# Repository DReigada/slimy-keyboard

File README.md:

# Slimy

a cool description for a cool keyboard

## TODO

- PCB
    - [ ] holes for feet?

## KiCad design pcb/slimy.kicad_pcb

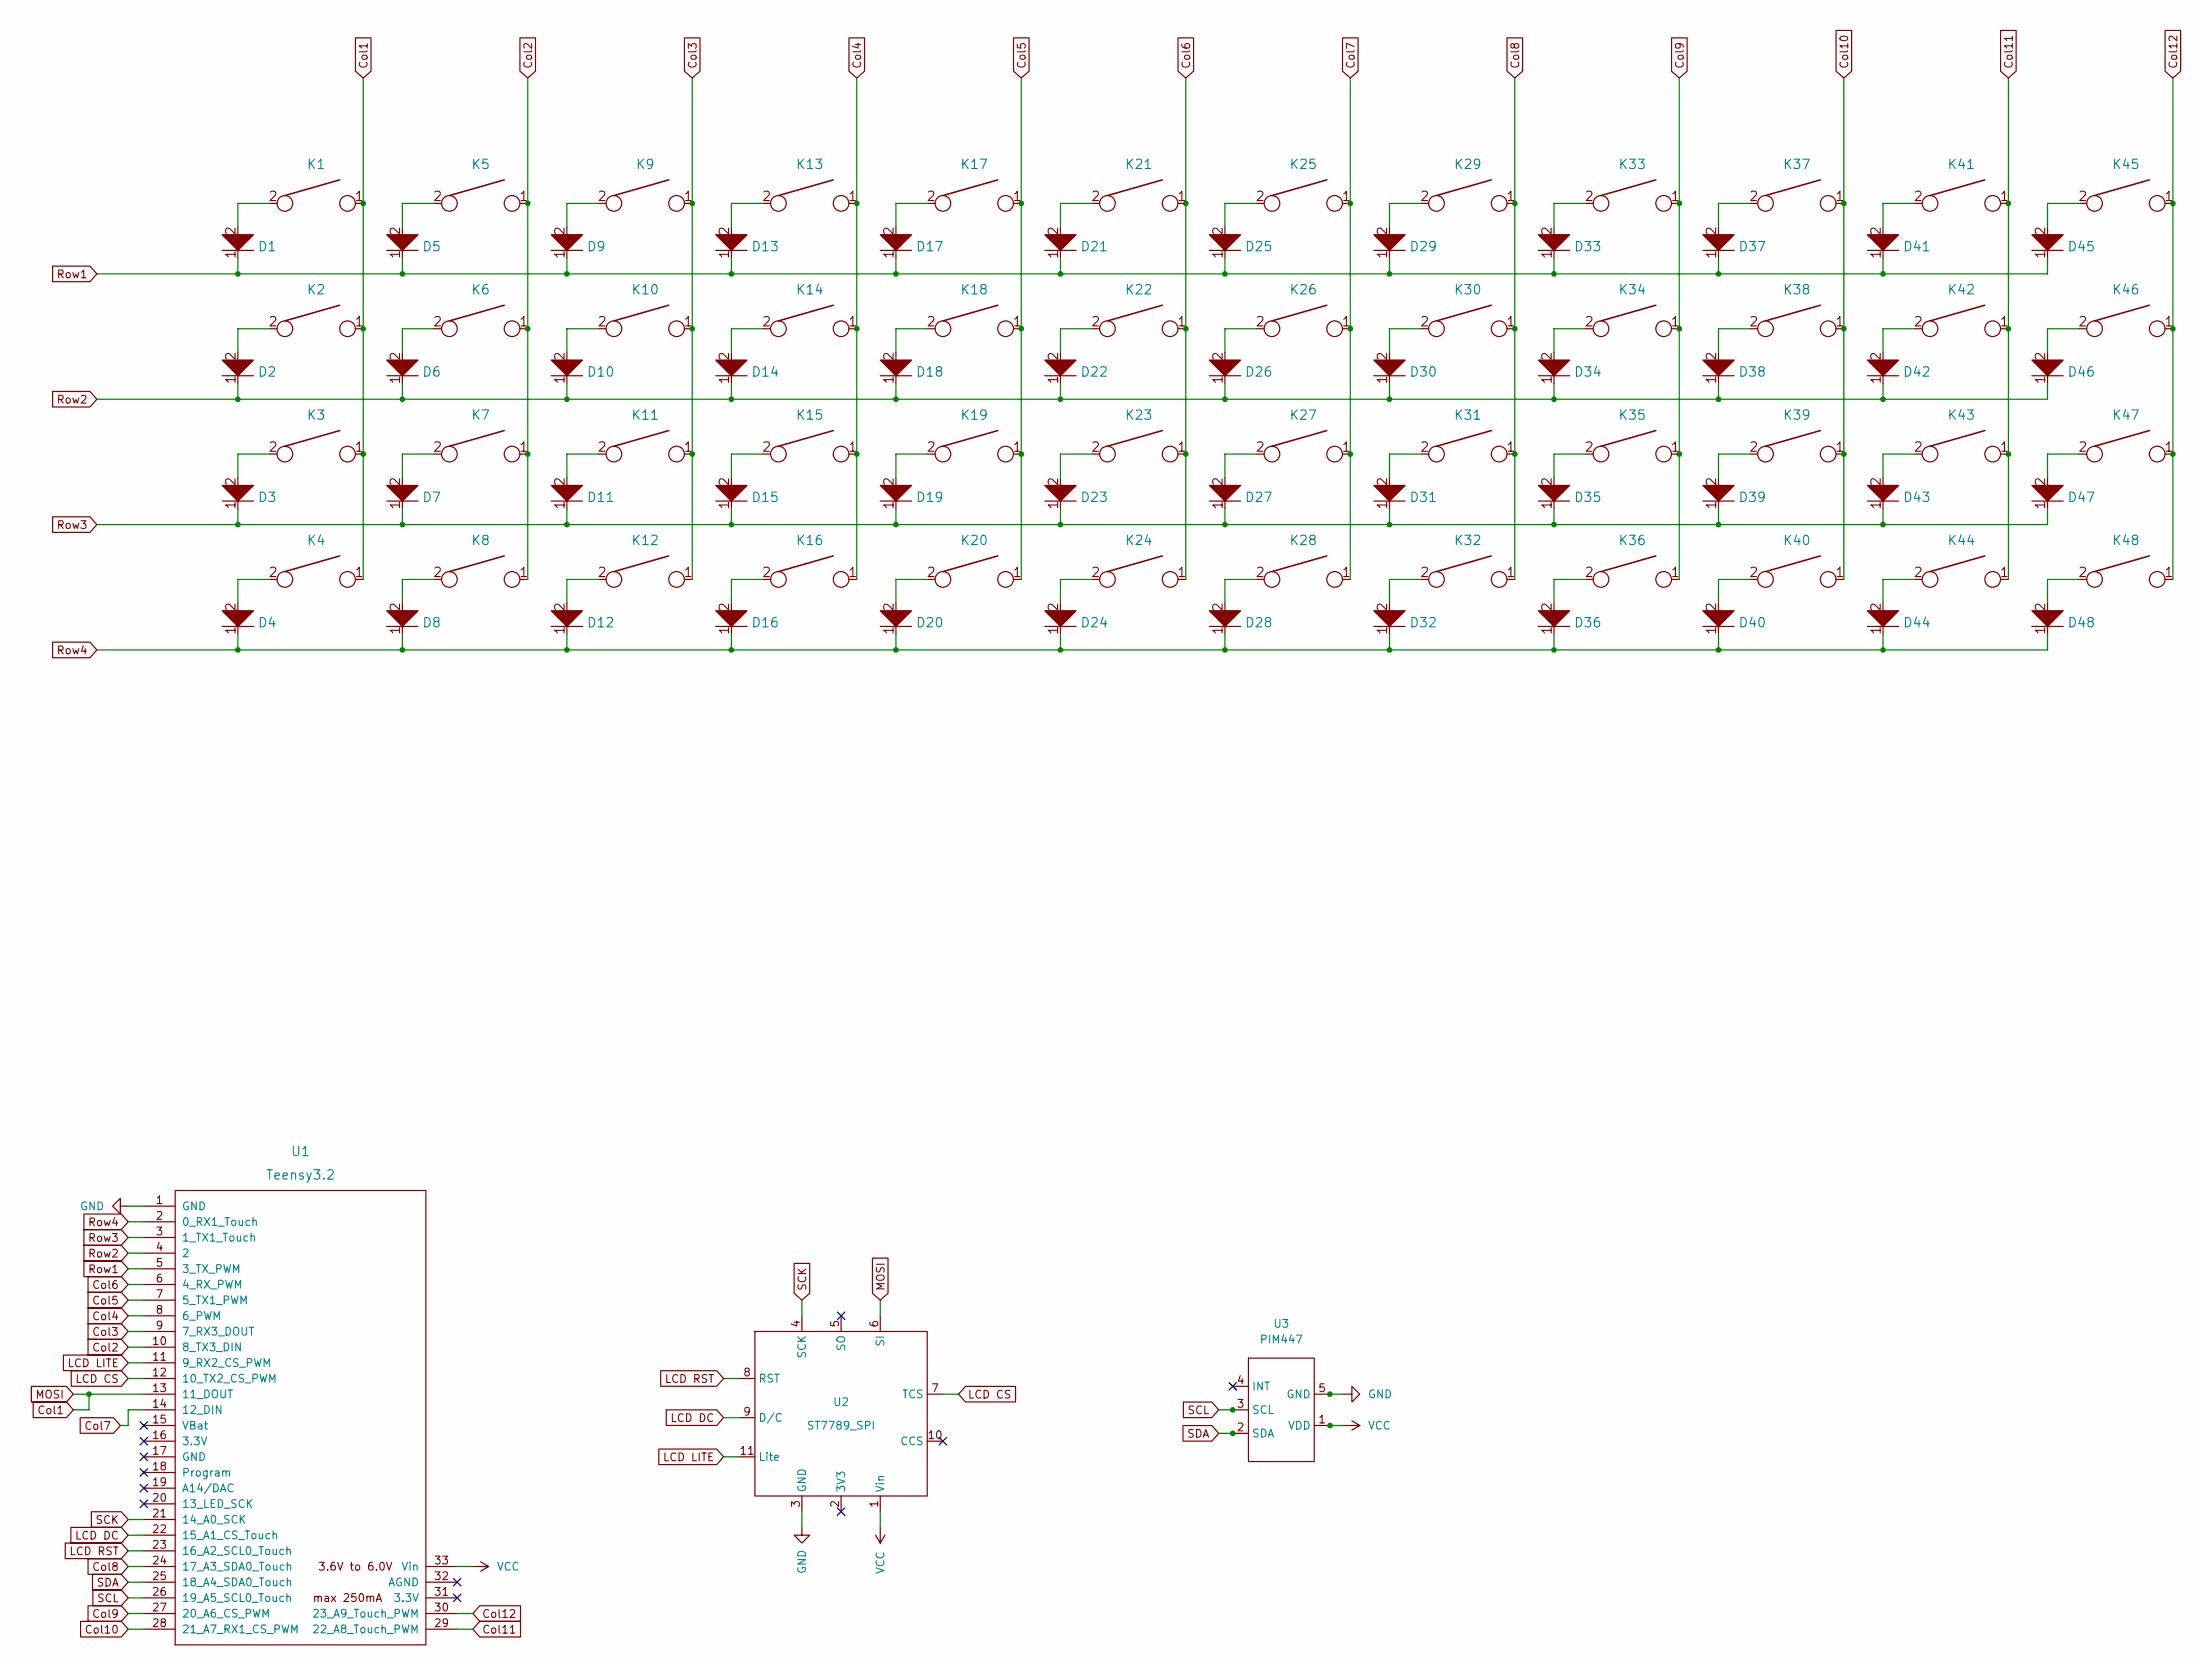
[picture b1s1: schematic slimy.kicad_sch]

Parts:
D1, D2, D3, D4, D5, D6, D7, D8, D9, D10, D11, D12, D13, D14, D15, D16, D17, D18, D19, D20, D21, D22, D23, D24, D25, D26, D27, D28, D29, D30, D31, D32, D33, D34, D35, D36, D37, D38, D39, D40, D41, D42, D43, D44, D45, D46, D47, D48: D
K1, K2, K3, K4, K5, K6, K7, K8, K9, K10, K11, K12, K13, K14, K15, K16, K17, K18, K19, K20, K21, K22, K23, K24, K25, K26, K27, K28, K29, K30, K31, K32, K33, K34, K35, K36, K37, K38, K39, K40, K41, K42, K43, K44, K45, K46, K47, K48: KEYSW; MX-1U-Hotswap-Antishear-flipped
U1: Teensy3.2; Teensy32
U2: ST7789_SPI; ST7789_1.3_240x240
U3: PIM447

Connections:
Col1: K1.1, K2.1, K3.1, K4.1, U1.13 (11_DOUT), U2.6 (SI)
Col2: K5.1, K6.1, K7.1, K8.1, U1.10 (8_TX3_DIN)
Col3: K9.1, K10.1, K11.1, K12.1, U1.9 (7_RX3_DOUT)
Col4: K13.1, K14.1, K15.1, K16.1, U1.8 (6_PWM)
Col5: K17.1, K18.1, K19.1, K20.1, U1.7 (5_TX1_PWM)
Col6: K21.1, K22.1, K23.1, K24.1, U1.6 (4_RX_PWM)
Col7: K25.1, K26.1, K27.1, K28.1, U1.14 (12_DIN)
Col8: K29.1, K30.1, K31.1, K32.1, U1.24 (17_A3_SDA0_Touch)
Col9: K33.1, K34.1, K35.1, K36.1, U1.27 (20_A6_CS_PWM)
Col10: K37.1, K38.1, K39.1, K40.1, U1.28 (21_A7_RX1_CS_PWM)
Col11: K41.1, K42.1, K43.1, K44.1, U1.29 (22_A8_Touch_PWM)
Col12: K45.1, K46.1, K47.1, K48.1, U1.30 (23_A9_Touch_PWM)
GND: U1.1 (GND), U2.3 (GND), U3.5 (GND)
LCD CS: U1.12 (10_TX2_CS_PWM), U2.7 (TCS)
LCD DC: U1.22 (15_A1_CS_Touch), U2.9 (D/C)
LCD LITE: U1.11 (9_RX2_CS_PWM), U2.11 (Lite)
LCD RST: U1.23 (16_A2_SCL0_Touch), U2.8 (RST)
unnamed: D1.2, K1.2
unnamed: D2.2, K2.2
unnamed: D3.2, K3.2
unnamed: D4.2, K4.2
unnamed: D5.2, K5.2
unnamed: D6.2, K6.2
unnamed: D7.2, K7.2
unnamed: D8.2, K8.2
unnamed: D9.2, K9.2
unnamed: D10.2, K10.2
unnamed: D11.2, K11.2
unnamed: D12.2, K12.2
unnamed: D13.2, K13.2
unnamed: D14.2, K14.2
unnamed: D15.2, K15.2
unnamed: D16.2, K16.2
unnamed: D17.2, K17.2
unnamed: D18.2, K18.2
unnamed: D19.2, K19.2
unnamed: D20.2, K20.2
unnamed: D21.2, K21.2
unnamed: D22.2, K22.2
unnamed: D23.2, K23.2
unnamed: D24.2, K24.2
unnamed: D25.2, K25.2
unnamed: D26.2, K26.2
unnamed: D27.2, K27.2
unnamed: D28.2, K28.2
unnamed: D29.2, K29.2
unnamed: D30.2, K30.2
unnamed: D31.2, K31.2
unnamed: D32.2, K32.2
unnamed: D33.2, K33.2
unnamed: D34.2, K34.2
unnamed: D35.2, K35.2
unnamed: D36.2, K36.2
unnamed: D37.2, K37.2
unnamed: D38.2, K38.2
unnamed: D39.2, K39.2
unnamed: D40.2, K40.2
unnamed: D41.2, K41.2
unnamed: D42.2, K42.2
unnamed: D43.2, K43.2
unnamed: D44.2, K44.2
unnamed: D45.2, K45.2
unnamed: D46.2, K46.2
unnamed: D47.2, K47.2
unnamed: D48.2, K48.2
Row1: D1.1, D5.1, D9.1, D13.1, D17.1, D21.1, D25.1, D29.1, D33.1, D37.1, D41.1, D45.1, U1.5 (3_TX_PWM)
Row2: D2.1, D6.1, D10.1, D14.1, D18.1, D22.1, D26.1, D30.1, D34.1, D38.1, D42.1, D46.1, U1.4 (2)
Row3: D3.1, D7.1, D11.1, D15.1, D19.1, D23.1, D27.1, D31.1, D35.1, D39.1, D43.1, D47.1, U1.3 (1_TX1_Touch)
Row4: D4.1, D8.1, D12.1, D16.1, D20.1, D24.1, D28.1, D32.1, D36.1, D40.1, D44.1, D48.1, U1.2 (0_RX1_Touch)
SCK: U1.21 (14_A0_SCK), U2.4 (SCK)
SCL: U1.26 (19_A5_SCL0_Touch), U3.3 (SCL)
SDA: U1.25 (18_A4_SDA0_Touch), U3.2 (SDA)
VCC: U1.33 (Vin), U2.1 (Vin), U3.1 (VDD)

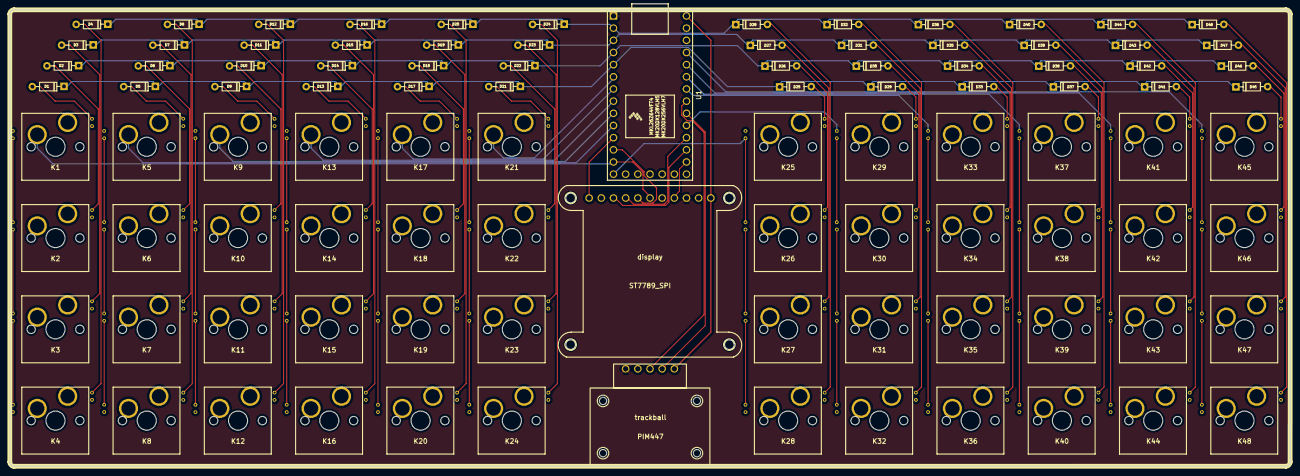
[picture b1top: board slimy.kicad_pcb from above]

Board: 2 copper layers, 267.2 x 95.3 mm, 100 parts (1 on the bottom side), 73 nets.

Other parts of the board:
kibuzzard-62A5BC49: G***; kibuzzard-62A5BC49

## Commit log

2022-04-21 WIP pcb design
2022-04-21 Add README
2022-04-23 WIP keyboard pcb design
2022-04-23 Add positioning script
2022-04-23 First iteration design
2022-04-24 First iteration design pt2
2022-04-25 Update pcb script
2022-04-25 Wire with PCB script
2022-04-25 Wire almost everything with script
2022-04-25 Wire everything switch related
2022-04-25 Cleanup
2022-04-25 Fix issues with updated pins
2022-04-26 Update diode footprint
2022-04-26 Round PBC corners
2022-06-12 Add logo
2022-06-12 Fix clearence problem
2022-06-12 Remove slimy test PCB
2022-06-12 Thicker logo lines
2022-06-12 Update readme todo
2022-06-12 Add keyboard name
2022-06-12 Fix screen and trackball footprints
2022-06-12 Fix keycap overlap with display
2022-06-12 Tweak some sizes
2022-06-12 Move logo
2022-06-19 Add border
2022-06-19 Add rev1 gerbers
